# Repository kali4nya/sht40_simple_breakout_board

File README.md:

# SHT40 Simple Breakout Board

A simple breakout board for the **Sensirion SHT40** temperature and humidity sensor, designed in [KiCad](https://www.kicad.org/).

This repository contains two PCB variants:

- **1 Board Version** – A single standalone SHT40 breakout board.
- **4 Board Version** – Four breakout boards panelized together, connected by breakaway tabs for easy separation after manufacturing.

Both versions include the complete KiCad design files and manufacturing outputs generated using the Fabrication Toolkit plugin for KiCad.

---

## PCB Versions

### 1. Single Board Version

A standalone SHT40 breakout board, designed for individual use.

**PCB Renders**

**Included Files**
- KiCad project (`.kicad_pro`)
- Schematic (`.kicad_sch`)
- PCB layout (`.kicad_pcb`)
- Production files (BOM, designators, IPC netlist and component positions)
- Gerber and drill files (ZIP archive)

---

### 2. Four Board Version

A panelized version containing four identical SHT40 breakout boards connected together using breakaway tabs.

The boards can be separated after manufacturing, allowing four individual breakout boards to be obtained from a single PCB panel.

**PCB Renders**

**Included Files**
- KiCad project (`.kicad_pro`)
- Schematic (`.kicad_sch`)
- PCB layout (`.kicad_pcb`)
- Production files (BOM, designators, IPC netlist and component positions)
- Gerber and drill files (ZIP archive)

---

## Schematic

Both PCB versions share the same electrical schematic.

---

## Repository Structure

```text
sht40_simple_breakout_board/
│
├── 1 board version/
│   ├── *.kicad_pro
│   ├── *.kicad_sch
│   ├── *.kicad_pcb
│   │
│   ├── production/
│   │   ├── bom.csv
│   │   ├── designators.csv
│   │   ├── netlist.ipc
│   │   ├── positions.csv
│   │   └── Gerber files.zip
│   │
│   └── pictures/
│       ├── pcb_front.png
│       ├── pcb_design.png
│       └── schematic.png
│
├── 4 board version/
│   ├── *.kicad_pro
│   ├── *.kicad_sch
│   ├── *.kicad_pcb
│   │
│   ├── production/
│   │   ├── bom.csv
│   │   ├── designators.csv
│   │   ├── netlist.ipc
│   │   ├── positions.csv
│   │   └── Gerber files.zip
│   │
│   └── pictures/
│       ├── pcb_front.png
│       └── pcb_design.png
│
├── README.md
└── LICENSE
```

---

## Manufacturing

Manufacturing files for both PCB variants are provided in their respective `production` directories.

The files were generated using the JLC **Fabrication Toolkit** plugin for KiCad and include:

| File | Description |
|---|---|
| `bom.csv` | Bill of Materials |
| `designators.csv` | Component designator information |
| `netlist.ipc` | IPC netlist |
| `positions.csv` | Component placement coordinates |
| Gerber ZIP | PCB fabrication layers and drill files |

These files are provided to make PCB manufacturing and assembly easier.

---

## Design Software

- **EDA:** KiCad 10.0
- **Manufacturing file generation:** Fabrication Toolkit for KiCad

---

## License

See the [LICENSE](LICENSE) file for the terms governing the use, modification and distribution of this project.

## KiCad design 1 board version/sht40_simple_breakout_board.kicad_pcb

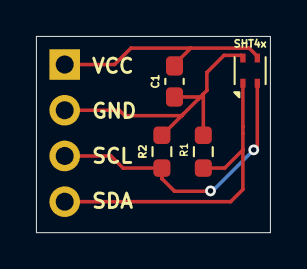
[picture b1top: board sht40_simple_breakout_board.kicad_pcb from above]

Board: 2 copper layers, 13.0 x 10.9 mm, 5 parts (1 on the bottom side), 4 nets.

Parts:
C1: 100nF; C_0603_1608Metric_Pad1.08x0.95mm_HandSolder
J1: Conn_01x04; PinHeader_1x04_P2.54mm_Vertical
R1, R2: 10k; R_0603_1608Metric_Pad0.98x0.95mm_HandSolder
U1: SHT4x; Sensirion_DFN-4_1.5x1.5mm_P0.8mm_SHT4x_NoCentralPad

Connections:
unnamed: C1.1, U1.3 (VDD)
unnamed: C1.2, R1.2, R2.2, U1.4 (VSS)
unnamed: R2.1, U1.2 (SCL)
unnamed: R1.1, U1.1 (SDA)

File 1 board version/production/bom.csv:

Designator,Footprint,Quantity,Value,LCSC Part #
C1,0603,1,100nF,
J1,PinHeader_1x04_P2.54mm_Vertical,1,Conn_01x04,
"R1, R2",0603,2,10k,
U1,Sensirion_DFN-4_1.5x1.5mm_P0.8mm_SHT4x_NoCentralPad,1,SHT4x,
